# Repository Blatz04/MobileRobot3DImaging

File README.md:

# MobileRobot3DImaging
3D imaging Mobile Robot

# 1. Introduction
# 2. Hardware
# 3. Firmware
# 4. Usage

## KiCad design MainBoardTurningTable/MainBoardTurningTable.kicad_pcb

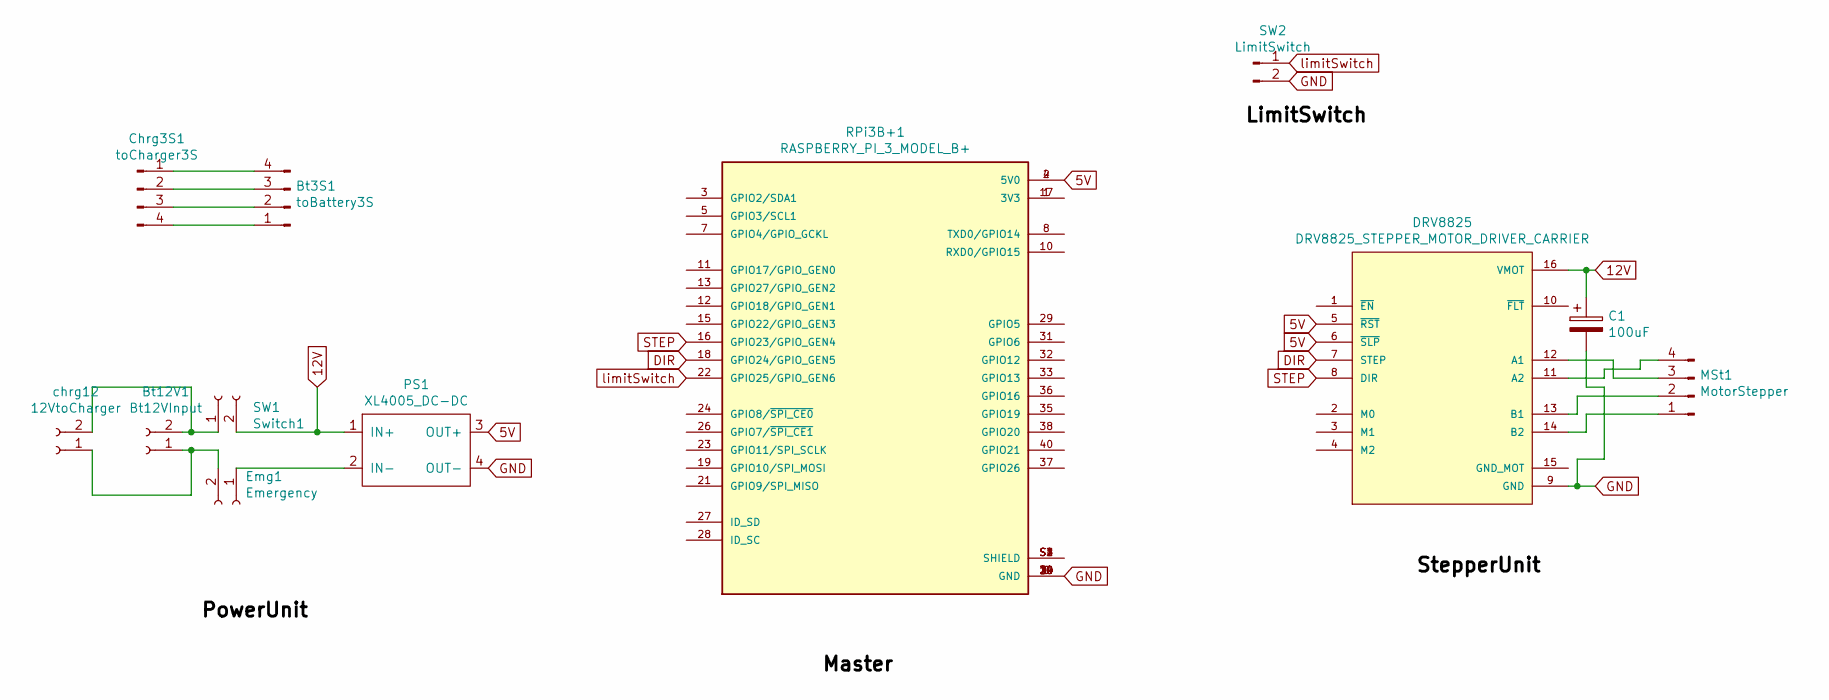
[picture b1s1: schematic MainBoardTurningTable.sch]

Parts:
Bt3S1: toBattery3S; Molex_KK-254_AE-6410-04A_1x04_P2.54mm_Vertical
Bt12V1: Bt12VInput; AMASS_XT30U-F_1x02_P5.0mm_Vertical
C1: 100uF; CP_Radial_D5.0mm_P2.50mm
Chrg3S1: toCharger3S; Molex_KK-254_AE-6410-04A_1x04_P2.54mm_Vertical
DRV8825: DRV8825_STEPPER_MOTOR_DRIVER_CARRIER; IC_DRV8825_STEPPER_MOTOR_DRIVER_CARRIER
Emg1: Emergency; SolderWire-1.5sqmm_1x02_P6mm_D1.7mm_OD3mm
MSt1: MotorStepper; Molex_KK-254_AE-6410-04A_1x04_P2.54mm_Vertical
PS1: XL4005_DC-DC
RPi3B+1: RASPBERRY_PI_3_MODEL_B+; MODULE_RASPBERRY_PI_3_MODEL_B+; PARTREV 1.0
SW1: Switch1; SolderWire-1.5sqmm_1x02_P6mm_D1.7mm_OD3mm
SW2: LimitSwitch; Molex_KK-254_AE-6410-02A_1x02_P2.54mm_Vertical
chrg12: 12VtoCharger; AMASS_XT30U-F_1x02_P5.0mm_Vertical

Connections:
5V: DRV8825.5 (~RST), DRV8825.6 (~SLP), PS1.3 (OUT+), RPi3B+1.2 (5V0), RPi3B+1.4 (5V0)
12V: C1.1, DRV8825.16 (VMOT), PS1.1 (IN+), SW1.2
DIR: DRV8825.7 (STEP), RPi3B+1.18 (GPIO24/GPIO_GEN5)
GND: C1.2, DRV8825.9 (GND), PS1.4 (OUT-), RPi3B+1.6 (GND), RPi3B+1.9 (GND), RPi3B+1.14 (GND), RPi3B+1.20 (GND), RPi3B+1.25 (GND), RPi3B+1.30 (GND), RPi3B+1.34 (GND), RPi3B+1.39 (GND), SW2.2
unnamed: Bt3S1.1, Chrg3S1.4
unnamed: Bt3S1.2, Chrg3S1.3
unnamed: Bt3S1.3, Chrg3S1.2
unnamed: Bt3S1.4, Chrg3S1.1
unnamed: Bt12V1.1, Emg1.2, chrg12.1
unnamed: Bt12V1.2, SW1.1, chrg12.2
unnamed: DRV8825.11 (A2), MSt1.4
unnamed: DRV8825.12 (A1), MSt1.3
unnamed: DRV8825.13 (B1), MSt1.2
unnamed: DRV8825.14 (B2), MSt1.1
unnamed: Emg1.1, PS1.2 (IN-)
unnamed: RPi3B+1.1 (3V3), RPi3B+1.17 (3V3)
unnamed: RPi3B+1.S1 (SHIELD), RPi3B+1.S2 (SHIELD), RPi3B+1.S3 (SHIELD), RPi3B+1.S4 (SHIELD)
STEP: DRV8825.8 (DIR), RPi3B+1.16 (GPIO23/GPIO_GEN4)
limitSwitch: RPi3B+1.22 (GPIO25/GPIO_GEN6), SW2.1

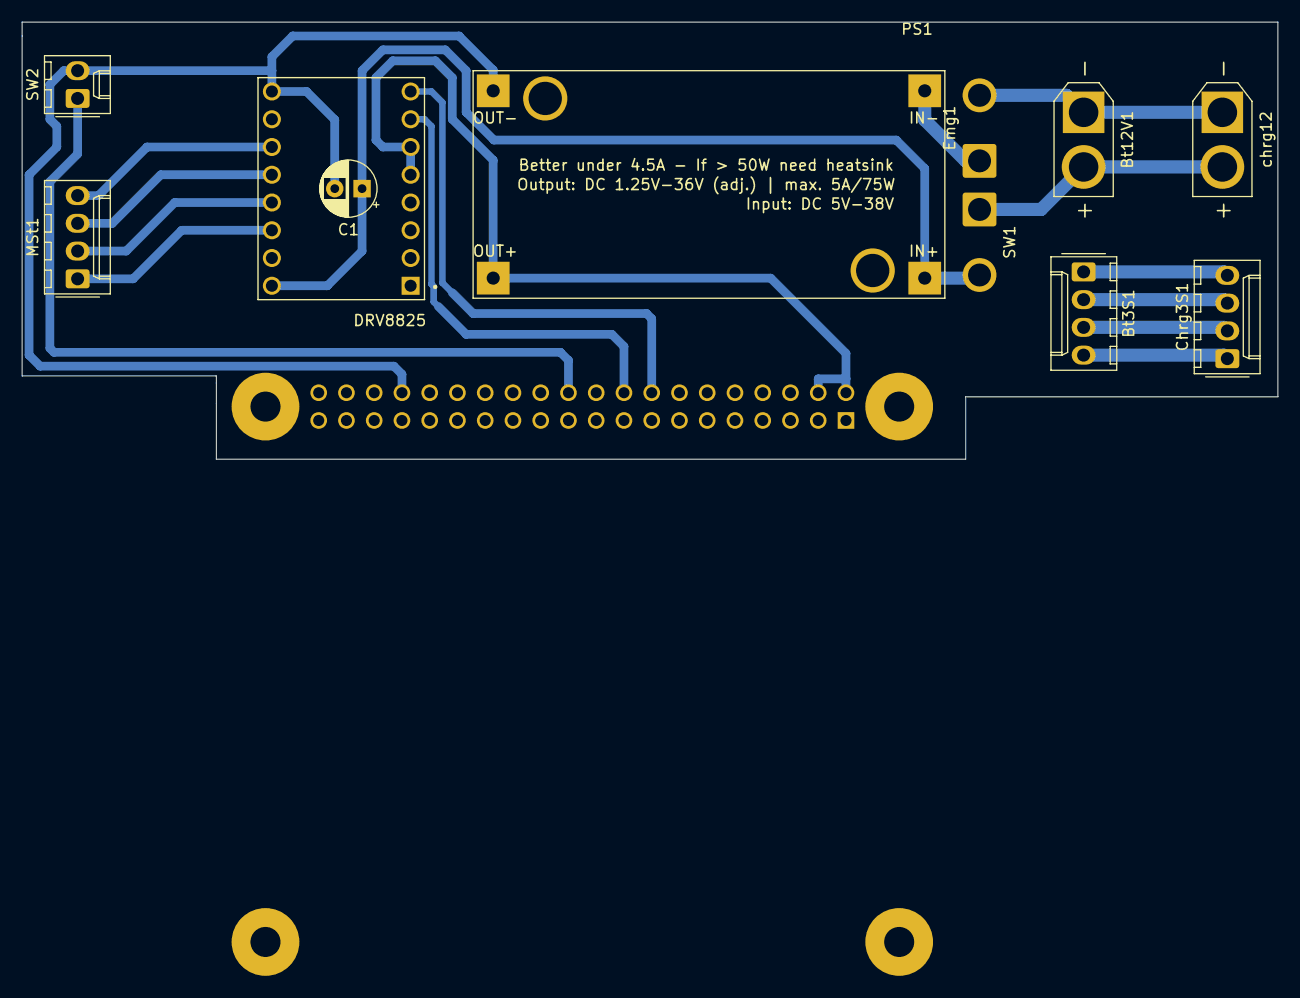
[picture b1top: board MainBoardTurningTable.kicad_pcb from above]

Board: 2 copper layers, 114.9 x 40.0 mm, 12 parts (1 on the bottom side), 19 nets.

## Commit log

2023-04-15 Add Mobile Robot position graph
2023-04-16 Nambah graph ke UI
